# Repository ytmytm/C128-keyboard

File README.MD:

# C128 USB Keyboard

This project is designed to allow a modern USB keyboard to be used with a Commodore 128D/DCR in place of the original Commodore keyboard.

This project was originally forked from [Hartland/C64-Keyboard](https://github.com/Hartland/C64-Keyboard).
I made extensive hardware and software changes to support the full C128 keyboard.

I kept only the USB interface, as PS/2 keyboards are becoming retro themselves.

This project requires a Seeed Studio XIAO SAMD21, which has a USB-C socket. I use a USB-C male to USB-A female OTG adapter to connect a standard PC keyboard.

-- Maciej 'YTM/Elysium' Witkowiak

# Features

- Works with compatible USB HID boot-protocol keyboards, including wireless models with USB receivers.
- Maps all C128 keys, including `40/80`, `CAPS` and the second set of cursor keys.
- Provides four keyboard layouts that can be switched on the fly.
- Supports a VICE-style joystick mode on the keypad, selected with NumLock or Shift+NumLock (may not work with some games).
- Supports an external power supply for an unmodified C128DCR.
- Supports an OLED display.
- Can be plugged directly into the keyboard port or mounted internally.

# PCB and schematic

Use KiCad to open the current [schematic](kicad-c128keyb/kicad-c128keyb.kicad_sch)
and [PCB](kicad-c128keyb/kicad-c128keyb.kicad_pcb) in the
[kicad-c128keyb](kicad-c128keyb/) folder. The legacy `kicad-c128keyb.sch` and
`.net` files describe an older Pro Micro/MT8808 design; use the `.kicad_sch`
and `.kicad_pcb` files for this XIAO/MT8816 adapter.

The [kicad-c128keyb/plots](kicad-c128keyb/plots) folder contains Gerber files ready for manufacturing
and a [PDF schematic](kicad-c128keyb/plots/kicad-c128keyb.pdf).

To order PCBs, open the [shared project on PCBWay](https://www.pcbway.com/project/shareproject/C128_USB_Keyboard_adapter_dcf19251.html) and add the boards to your cart.

## Parts

* Seeed Studio XIAO SAMD21 (SAMD21, not RP2040)
* U1: MT8816 or MT8812
* U2: 74HC/HCT/LS595
* R1, R2, R3: 10 kΩ resistors
* Q1, Q2, Q3: 2N3904 transistors (or another NPN type, such as S9013)
* C1, C2: 100 nF capacitors
* PCB-mount male DB25 connector (option 1)
* 26-pin ribbon cable connector / 2 × 13-pin headers (option 2)
* Pin headers and sockets
* 128 × 32 SSD1306 I²C OLED display (optional)

Check the pinout of any substitute NPN transistor before fitting it to the PCB.

## Connection options

- Plugs directly into the keyboard port when fitted with a male DB25 connector.
- Can use a ribbon cable for either an internal or external connection.
- Can be powered from the keyboard port or an external source, selected by a jumper.
- Can be fitted with a 128 × 32 I²C OLED display for status and debugging.

### Power (C128DCR only)

The C128D supplies +5 V on pin 4 of the keyboard port; the C128DCR does not.
An internal modification can add this connection to the C128DCR.

The photo below shows a wire on the underside of the C128DCR mainboard connecting +5 V from the joystick port to pin 4 of the keyboard port.

If you prefer not to open your C128DCR, you can supply external power from the nearby cassette or joystick port.
In this case, leave jumper JP1 open and connect +5 V to the `Ext. power` connector. Observe the polarity.

Options:

- JP1 open: supply power through `Ext. power` for an unmodified C128DCR.
- JP1 closed: leave `Ext. power` disconnected; use this setting for a C128D or a modified C128DCR.

### Flat cable: 26 pins (socket) to 25 pins (DB25 male)

If you prefer not to have the adapter protruding from the computer, you can make an extension cable.

You need:

* A 26-wire ribbon cable
* 26-pin ribbon cable connectors (a male PCB connector and a female cable connector)
* A male DB25 insulation-displacement connector for ribbon cable

Steps:

1. Solder the 26-pin male ribbon cable connector to J1.
2. Crimp the 26-pin female connector onto the cable, aligning the red wire (wire 1) with the triangular pin-1 mark.
3. Separate wire 26 (at the opposite edge from the red wire) from the ribbon and cut it as close to the female connector as possible.
4. Align the cable with the DB25 connector and crimp it, checking that the red wire connects to pin 1.

# Firmware

The sketch is in [SEEED/C128_keyboard](SEEED/C128_keyboard/). Keep all files in
that folder together when copying it to another computer.

## Install and upload with Arduino IDE

1. Install the **Seeed SAMD Boards** package and select the **Seeeduino XIAO**
   board (SAMD21). Follow the [Seeed setup instructions](https://wiki.seeedstudio.com/Seeeduino-XIAO/#software)
   to add the board package URL if necessary.
2. Use the Library Manager to install **[U8g2](https://github.com/olikraus/U8g2_Arduino)**
   and **[ShiftRegister74HC595](https://github.com/Simsso/ShiftRegister74HC595)**.
   U8g2 is required to compile the sketch even when no OLED is connected.
3. Download **`SEEED/C64_USB_Host_Library_SAMD.zip` from this repository**
   ([download the matching ZIP](SEEED/C64_USB_Host_Library_SAMD.zip)). In the IDE,
   choose **Sketch > Include Library > Add .ZIP Library** and select that local
   file. Alternatively, replace the installed library with this checkout's
   [source directory](SEEED/C64_USB_Host_Library_SAMD).
   A generic USB host library is not a substitute for this modified version.
4. Open [C128_keyboard.ino](SEEED/C128_keyboard/C128_keyboard.ino) in the Arduino IDE.
5. Disconnect the USB keyboard/OTG adapter and connect the XIAO's USB-C port
   to the computer with a USB data cable. Select the board's port and upload.
   If the port is missing or upload fails, enter the bootloader as described
   below, select its port, and try again.
6. Disconnect the programming cable, reconnect the keyboard through the OTG
   adapter, and power the adapter using the configuration described above.

Install the matching USB library on **the computer that compiles the sketch**.
Updating only the sketch or the Git checkout does not update an independently
installed library. The sketch rejects older library headers at compile time.

### Replacing the library on Windows

1. Close Arduino IDE and locate the sketchbook folder shown in its Preferences.
   Its library directory is usually `Documents\Arduino\libraries`, but the
   sketchbook may be elsewhere, including under OneDrive.
2. Move the old `C64_USB_Host_Library_SAMD` folder outside the `libraries`
   directory, then extract the current ZIP there. Replace the whole folder.
3. Check that the resulting layout is
   `libraries\C64_USB_Host_Library_SAMD\library.properties`, with no extra
   nested `C64_USB_Host_Library_SAMD` directory.
4. Restart the IDE and compile again. If multiple libraries are reported for
   `KeyboardController.h`, enable verbose compilation output and check the
   selected path. Remove or replace any outdated copy being selected.

On systems that support symbolic links, the installed library directory can
instead link to this checkout's `SEEED/C64_USB_Host_Library_SAMD` directory.
Move the old copy outside `libraries` and restart the IDE after changing it.

## Compile with the checkout's library using Arduino CLI

Run from the repository root. The Seeed SAMD board package, U8g2 and
ShiftRegister74HC595 must already be installed for Arduino CLI.

Bash (Linux/macOS):

```sh
arduino-cli compile \
  --fqbn Seeeduino:samd:seeed_XIAO_m0 \
  --library "$PWD/SEEED/C64_USB_Host_Library_SAMD" \
  SEEED/C128_keyboard
```

PowerShell (Windows):

```powershell
arduino-cli compile --fqbn Seeeduino:samd:seeed_XIAO_m0 --library ".\SEEED\C64_USB_Host_Library_SAMD" ".\SEEED\C128_keyboard"
```

The explicit [`--library` option](https://arduino.github.io/arduino-cli/1.5/sketch-build-process/#dependency-resolution)
has priority over libraries installed in the sketchbook. These commands use
the source directory directly, so no USB library ZIP installation is needed.
They compile the firmware; use the Arduino IDE or an appropriate CLI upload
command to upload it to the board.

## Entering the bootloader (double reset)

The original XIAO SAMD21 has reset pads rather than an onboard reset button.
To enter its bootloader:

1. Disconnect the keyboard/OTG adapter and connect the XIAO to the computer
   with a USB data cable.
2. Briefly bridge the two **RST reset pads twice in quick succession**, removing
   the bridge between the two touches. See [Seeed's reset-pad illustration](https://wiki.seeedstudio.com/Seeeduino-XIAO/#enter-bootloader-mode)
   for the pad locations. If your board has a reset button, press it twice.
3. The bootloader LED should pulse. With a UF2-enabled bootloader, a removable
   drive normally named **Arduino** appears, containing `INFO_UF2.TXT`.
   A bootloader serial port may also appear; on Windows its COM number may
   differ from the application port. Select that port for an IDE upload.

A single reset restarts the application. **Print Screen on the USB keyboard
only resets the adapter's keys and settings; it does not enter the bootloader.**

## Uploading a UF2 file by copying it to the boot drive

The [XIAO SAMD21 UF2 bootloader supports drag-and-drop flashing](https://wiki.seeedstudio.com/Seeeduino-XIAO-CircuitPython/#installing-circuitpython).
With a UF2-enabled bootloader and a UF2 build of **this project's firmware for
XIAO SAMD21**, no Arduino IDE is needed on the computer doing the upload:

1. Enter the bootloader using the double-reset procedure above.
2. Copy the firmware `.uf2` file to the **Arduino** removable drive using
   Windows File Explorer or your system's file manager.
3. Wait for copying to finish. The board normally restarts automatically and
   the boot drive disappears. Reconnect the keyboard/OTG adapter for use.

Prebuilt firmware is produced by the [Firmware build workflow](.github/workflows/firmware.yml)
and can be downloaded from a successful Actions run or a GitHub Release after
its build completes. The UF2 already contains the compiled libraries; its
recipient does not need Arduino IDE or the USB library ZIP.

Compiled binaries are not tracked in Git. The library ZIP is installed on the
build computer; it is not copied to the board's boot drive.
A `.bin` file cannot be used by simply renaming it to `.uf2`.

### Creating a UF2 from an Arduino build

1. Build for **Seeeduino XIAO (SAMD21)** with the matching USB library, then
   use **Sketch > Export Compiled Binary** in the Arduino IDE. Locate the
   application binary, normally named `C128_keyboard.ino.bin`.
2. Download [uf2conv.py](https://github.com/microsoft/uf2/blob/master/utils/uf2conv.py)
   and [uf2families.json](https://github.com/microsoft/uf2/blob/master/utils/uf2families.json)
   from Microsoft's UF2 project and place them alongside the binary.
3. In that directory, run the conversion with Python 3 (adjust the binary
   filename if your build uses a different one):

   ```sh
   python uf2conv.py --convert --family SAMD21 --base 0x2000 --output C128_keyboard.uf2 C128_keyboard.ino.bin
   ```

Use the application binary from this sketch's XIAO SAMD21 build, without a
bootloader image prepended. The `0x2000` application address matches the
[Seeed XIAO linker configuration](https://github.com/Seeed-Studio/ArduinoCore-samd/blob/master/variants/XIAO_m0/linker_scripts/gcc/flash_with_bootloader.ld).
The conversion only creates the UF2 file; copy it to the boot drive separately.

## OLED and firmware version

The optional display is a **128 × 32 SSD1306 I²C OLED at address `0x3C`**.
The firmware probes for it at startup and skips display operations if it does
not respond. The keyboard and joystick functions work without it.

The OLED shows the firmware release date below startup USB status messages,
for example `USB Configuring` / `FW 2026-10-30`. The version also appears below
`USB Running`. Status messages are cleared after about five seconds of
inactivity; key events replace them with the key display.

Set the release date in [firmware_version.h](SEEED/C128_keyboard/firmware_version.h)
when preparing a new firmware release. Recompiling the same source does not
change its version.

## Keyboard compatibility

The USB driver uses HID boot-protocol reports with six ordinary key slots and
separate modifier bits. A keyboard that only supports a proprietary or
NKRO-only report format may not work. Wireless keyboards need a compatible
USB receiver; Bluetooth-only keyboards cannot connect directly.

The adapter reads raw USB HID usages, so the PC's operating-system keyboard
layout does not configure it. The symbolic maps assume US-style key labels.
For troubleshooting, Right Shift should appear as HID usage `0xE5` with
modifier mask `0x20`. `getOemKey()` returns the HID usage; `getKey()` returns
ASCII and is not used to map the Commodore keyboard matrix.

# Keyboard mapping

Key maps are defined in [SEEED/C128_keyboard/keymaps.h](SEEED/C128_keyboard/keymaps.h). You can modify existing ones or add your own.

After defining a new keymap, add it to the `keymaps[]` array at the bottom of the file. The first entry is the default layout.

Press **Pause** to cycle through C128 positional → C128 symbolic → C64
positional → C64 symbolic → C128 positional. Startup and **Print Screen**
reset select C128 positional. Selection is not saved across power cycles.
The C64 names describe keyboard layouts; the hardware still uses the C128D/DCR
keyboard connector.

The following controls apply in all four layouts:

| USB key | Action |
| --- | --- |
| Print Screen | Reset adapter keys and settings to startup defaults; does not reset the C128 |
| Scroll Lock | Toggle Shift Lock |
| Pause | Select the next keymap |
| Caps Lock | RUN/STOP; use Scroll Lock for Shift Lock |
| Page Up or AltGr | Hold RESTORE while the key is held |
| NumLock | Toggle joystick mode and select port 2 |
| Shift+NumLock | Toggle joystick mode and select port 1 |

After resetting the adapter, release any keys that were held during the reset.
Disconnecting the USB keyboard releases held keys, joystick outputs, RESTORE
and Shift Lock, but preserves the selected keymap and joystick mode.

## C128 positional (default)

The top row follows the C128 keyboard layout. This layout is useful if you are familiar with the original keyboard.

| USB key | C128 key |
|---------|----------|
| ESC | RUN/STOP |
| Tab | CTRL |
| Caps Lock | RUN/STOP |
| F1 | ESC |
| F2 | TAB |
| F3 | ALT |
| F4 | CAPS/DIN (toggle) |
| F5 | HELP |
| F6 | LINEFEED |
| F7 | 40/80 (toggle) |
| F8 | NO SCROLL |
| F9 | F1/F2 |
| F10 | F3/F4 |
| F11 | F5/F6 |
| F12 | F7/F8 |
| Print Screen | reset adapter keys and settings |
| Scroll Lock | Shift Lock |
| Pause | switch to next keymap |
| Insert | POUND |
| Home | CLR/HOME |
| Page Up | RESTORE |
| End | RUN/STOP |
| NumLock | enable/disable joystick #2 on keypad |
| Shift+NumLock | enable/disable joystick #1 on keypad |
| Keypad digits, `+`, `-`, Enter and `.` | C128 keypad equivalents (outside joystick mode) |
| left CTRL | C= key |
| left SHIFT | left SHIFT |
| left ALT | C128 top cursor down |
| left Win | C128 top cursor up |
| Menu/Application | C128 top cursor left |
| right CTRL | C128 top cursor right |
| right SHIFT | right SHIFT |
| AltGr | RESTORE |
| right Win | ignored |

## C128 symbolic

Symbols follow US-style PC keycaps; for example, Shift+2 produces `@` rather than `"`.

Other changes:

- C128 top cursor keys are available via Shift+arrow keys.
- Both Ctrl keys map to CTRL.
- Both Windows keys map to the C= key.
- Left Alt maps to C128 ALT.
- AltGr maps to RESTORE.

The function row and several editing keys also differ from C128 positional:

| USB key | C128 key/action |
| --- | --- |
| Esc | ESC |
| Tab | TAB |
| F1–F8 | F1–F8 (even function keys use synthetic Shift) |
| F9 | HELP |
| F10 | NO SCROLL |
| F11 | 40/80 (toggle) |
| F12 | CAPS/DIN (toggle) |
| Insert | INST/DEL with Shift (insert) |
| Delete | INST/DEL |
| Shift+Return | LINEFEED |

Menu/Application still maps to the C128 top left cursor key.

## C64 positional

This uses the positional character and modifier mappings, with these changes:

- Keypad digits, `+`, `-`, Enter and `.` map to the Commodore's main digit
  keys, PLUS, MINUS, RETURN and full stop.
- F1–F8 map to the corresponding Commodore function keys, using synthetic
  Shift for even-numbered function keys.
- F9 and F10 are ignored.
- F11 toggles 40/80; F12 toggles CAPS/DIN.

For this reason, the C128 positional function-row table does not apply to this
layout. The common adapter controls and joystick mode are still available.

## C64 symbolic

This uses the C128 symbolic mapping, except that keypad digits, `+`, `-`,
Enter and `.` map to the Commodore's main digit keys, PLUS, MINUS,
RETURN and full stop. Joystick mode overrides keypad direction and FIRE
keys in the same way as in the other layouts.

# Joystick mode

Press **NumLock** to toggle joystick mode and select port 2, or
**Shift+NumLock** to toggle it and select port 1. Both combinations toggle
the same on/off state. To change ports while the mode is enabled, first
turn it off, then enable the desired port with the appropriate combination.

The OLED reports the selected mode and port. The USB library toggles the
NumLock LED separately; it is not resynchronised when Print Screen resets
the adapter, so the LED alone is not a reliable mode indicator after a reset.

The keypad directions are the same for both joystick ports:

| Keypad key | Direction |
| --- | --- |
| 7 | up + left |
| 8 | up |
| 9 | up + right |
| 4 | left |
| 6 | right |
| 1 | down + left |
| 2 | down |
| 3 | down + right |
| 5, 0, right Ctrl | FIRE |

A diagonal key is equivalent to holding its two direction keys together.
A direction remains active while any held key still requires it. For example,
releasing keypad 1 while holding keypad 4 leaves LEFT active.

This mode is not intended to replace a physical joystick: some games may interpret joystick #2 inputs as keypresses.

# Automated builds and releases

[.github/workflows/firmware.yml](.github/workflows/firmware.yml) runs host tests
and builds for **XIAO SAMD21** on firmware-related pushes, pull requests,
manual Actions runs, and published GitHub Releases. It explicitly selects the
USB library from this checkout. Arduino CLI, the board package, external
libraries and the official UF2 converter are pinned to specific versions.

Each successful run provides a downloadable artifact containing:

- `.uf2` for copying to the bootloader drive;
- `.bin` application image and `.elf` debug symbols;
- `.json` with the firmware date, source commit and tool versions;
- `SHA256SUMS.txt` for integrity checks.

Filenames contain the board name, firmware date and abbreviated source commit.
Actions artifacts are retained for 30 days. For a lasting download, publish a
GitHub Release from a tag named **`YYYY-MM-DD` or `vYYYY-MM-DD`**, matching
[firmware_version.h](SEEED/C128_keyboard/firmware_version.h), for example
`v2026-10-30`. The workflow rebuilds the tagged source and attaches the files
to that release after tests and verification pass. A tag/date mismatch fails
the build instead of attaching incorrectly labelled files.

Publishing a release is a manual maintainer action; branch pushes and pull
requests only produce build artifacts. The workflow does not create releases
or push tags. To change the tested dependency versions, edit the workflow's
`env` section and rerun the build.

## Release checklist (maintainers)

**Use `v<firmwareVersion>` as the release tag.** For example, if
`firmware_version.h` contains `"2026-10-30"`, use **`v2026-10-30`**.

1. Set the release date in [firmware_version.h](SEEED/C128_keyboard/firmware_version.h).
2. Commit and push the source, including that version and the workflow.
3. On GitHub, open **Releases > Draft a new release**. Select or create the
   tag `vYYYY-MM-DD` using the exact date from the header. Point the tag at
   the tested commit/branch containing the updated firmware and workflow.
4. Click **Publish release**. Saving a draft alone does not start this build.
5. Wait for **Firmware build** to succeed and check that the release has its
   `.uf2` and `SHA256SUMS.txt` assets before sharing it.

The packager also accepts the date without the `v` prefix, but use the
`vYYYY-MM-DD` convention for project releases. A different date is rejected.

The packager checks the application's vector table, SAMD21 family ID, flash
addresses and every UF2 payload byte against the compiled BIN. These checks
validate the file format and target; hardware testing is still required.

# Development and tests

With Python 3 and GCC's `g++` with AddressSanitizer and UndefinedBehaviorSanitizer
available (for example, on Linux or WSL), run from the repository root:

```sh
python3 tests/test_keyboard_events.py
python3 -m unittest discover -s tests -p 'test_firmware_artifacts.py' -v
```

The host tests compile the actual event-handling functions as C++14, with
`-Wall -Wextra -Werror`. They use mocked USB transport, GPIO and OLED drawing;
they do not replace an Arduino build or a hardware test. See
[tests/README.md](tests/README.md) for coverage and hardware checks.

After changing the bundled USB library, rebuild its tracked ZIP:

```sh
python3 tools/package_usb_library.py
```

The host tests verify that the ZIP matches the source directory. Both must
be committed together when that library changes. Firmware-only changes do
not require a new USB library ZIP. On Windows, use `python` instead of
`python3` if that is the installed command name.

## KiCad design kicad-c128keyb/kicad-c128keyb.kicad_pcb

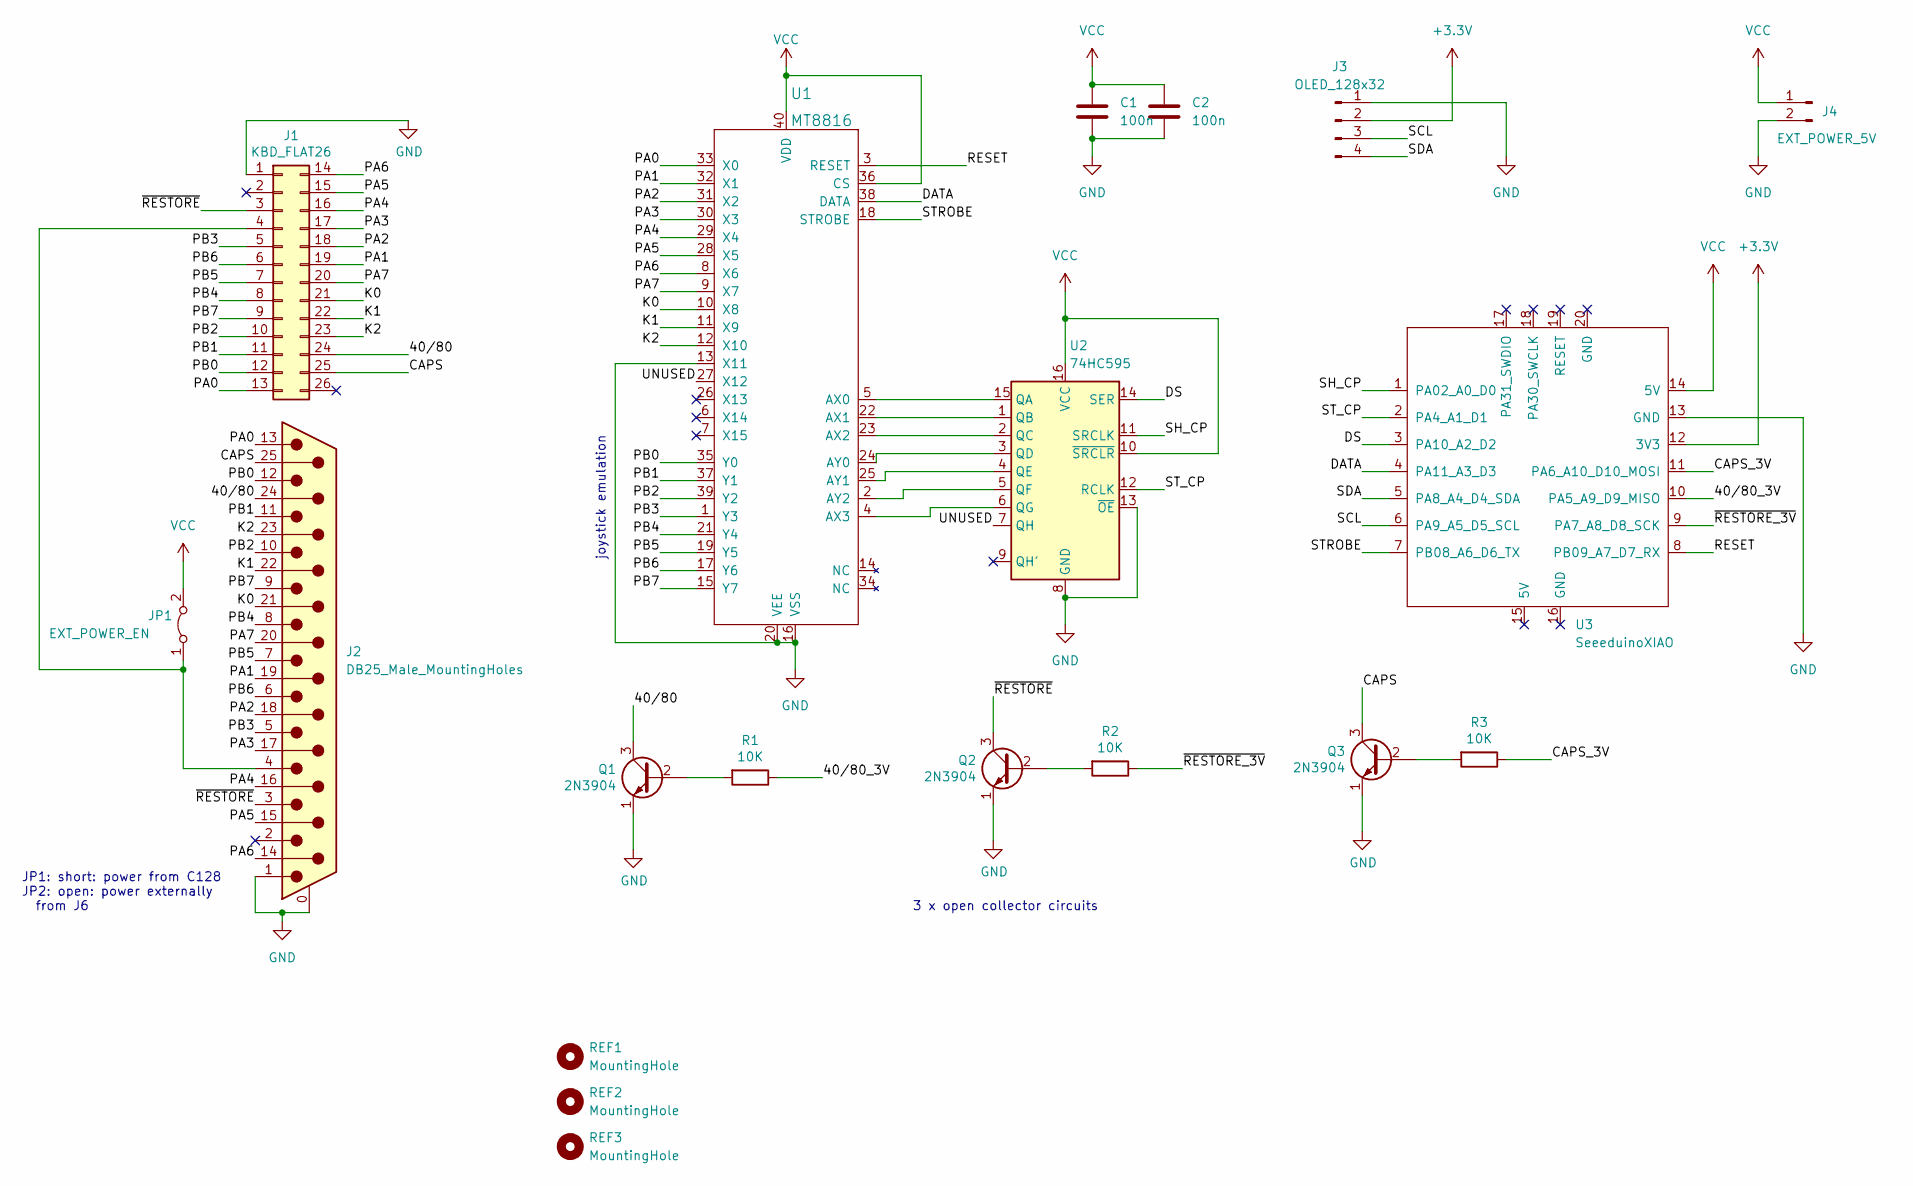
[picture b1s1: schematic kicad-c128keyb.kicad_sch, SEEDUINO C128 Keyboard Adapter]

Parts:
C1, C2: 100n; C_Disc_D4.3mm_W1.9mm_P5.00mm
J1: KBD_FLAT26; PinHeader_2x13_P2.54mm_Vertical
J2: DB25_Male_MountingHoles; DSUB-25_Male_Horizontal_P2.77x2.84mm_EdgePinOffset4.94mm_Ho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
J3: OLED_128x32; PinHeader_1x04_P2.54mm_Vertical
J4: EXT_POWER_5V; PinHeader_1x02_P2.54mm_Vertical
JP1: EXT_POWER_EN; PinHeader_1x02_P2.54mm_Vertical
Q1, Q2, Q3: 2N3904; TO-92_Inline
R1, R2, R3: 10K; R_Axial_DIN0207_L6.3mm_D2.5mm_P7.62mm_Horizontal
REF1, REF2, REF3: MountingHole; MountingHole_2.2mm_M2_Pad_Via
U1: MT8816; DIP-40_W15.24mm_Socket
U2: 74HC595; DIP-16_W7.62mm_Socket
U3: SeeeduinoXIAO; XIAO-Generic-Hybrid-14P-2.54-21X17.8MM

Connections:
+3V3: J3.2, U3.12 (3V3)
/40/80: J1.24, J2.24, Q1.3 (C)
/40/80_3V: R1.1, U3.10 (PA5_A9_D9_MISO)
/CAPS: J1.25, J2.25, Q3.3 (C)
/CAPS_3V: R3.1, U3.11 (PA6_A10_D10_MOSI)
/DATA: U1.38 (DATA), U3.4 (PA11_A3_D3)
/DS: U2.14 (SER), U3.3 (PA10_A2_D2)
/K0: J1.21, J2.21, U1.10 (X8)
/K1: J1.22, J2.22, U1.11 (X9)
/K2: J1.23, J2.23, U1.12 (X10)
/PA0: J1.13, J2.13, U1.33 (X0)
/PA1: J1.19, J2.19, U1.32 (X1)
/PA2: J1.18, J2.18, U1.31 (X2)
/PA3: J1.17, J2.17, U1.30 (X3)
/PA4: J1.16, J2.16, U1.29 (X4)
/PA5: J1.15, J2.15, U1.28 (X5)
/PA6: J1.14, J2.14, U1.8 (X6)
/PA7: J1.20, J2.20, U1.9 (X7)
/PB0: J1.12, J2.12, U1.35 (Y0)
/PB1: J1.11, J2.11, U1.37 (Y1)
/PB2: J1.10, J2.10, U1.39 (Y2)
/PB3: J1.5, J2.5, U1.1 (Y3)
/PB4: J1.8, J2.8, U1.21 (Y4)
/PB5: J1.7, J2.7, U1.19 (Y5)
/PB6: J1.6, J2.6, U1.17 (Y6)
/PB7: J1.9, J2.9, U1.15 (Y7)
/RESET: U1.3 (RESET), U3.8 (PB09_A7_D7_RX)
/SCL: J3.3, U3.6 (PA9_A5_D5_SCL)
/SDA: J3.4, U3.5 (PA8_A4_D4_SDA)
/SH_CP: U2.11 (SRCLK), U3.1 (PA02_A0_D0)
/STROBE: U1.18 (STROBE), U3.7 (PB08_A6_D6_TX)
/ST_CP: U2.12 (RCLK), U3.2 (PA4_A1_D1)
/UNUSED: U1.27 (X12), U2.7 (QH)
/~RESTORE_3V: R2.1, U3.9 (PA7_A8_D8_SCK)
/~RESTORE: J1.3, J2.3, Q2.3 (C)
GND: C1.2, C2.2, J1.1, J2.0 (PAD), J2.1, J3.1, J4.2, Q1.1 (E), Q2.1 (E), Q3.1 (E), U1.13 (X11), U1.16 (VSS), U1.20 (VEE), U2.8 (GND), U2.13 (~OE), U3.13 (GND)
unnamed: J1.4, J2.4, JP1.1 (A)
unnamed: Q1.2 (B), R1.2
unnamed: Q2.2 (B), R2.2
unnamed: Q3.2 (B), R3.2
unnamed: U1.2 (AY2), U2.5 (QF)
unnamed: U1.4 (AX3), U2.6 (QG)
unnamed: U1.5 (AX0), U2.15 (QA)
unnamed: U1.22 (AX1), U2.1 (QB)
unnamed: U1.23 (AX2), U2.2 (QC)
unnamed: U1.24 (AY0), U2.3 (QD)
unnamed: U1.25 (AY1), U2.4 (QE)
VCC: C1.1, C2.1, J4.1, JP1.2 (B), U1.36 (CS), U1.40 (VDD), U2.10 (~SRCLR), U2.16 (VCC), U3.14 (5V)

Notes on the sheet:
joystick emulation
JP1: short: power from C128 JP2: open: power externally from J6
3 x open collector circuits

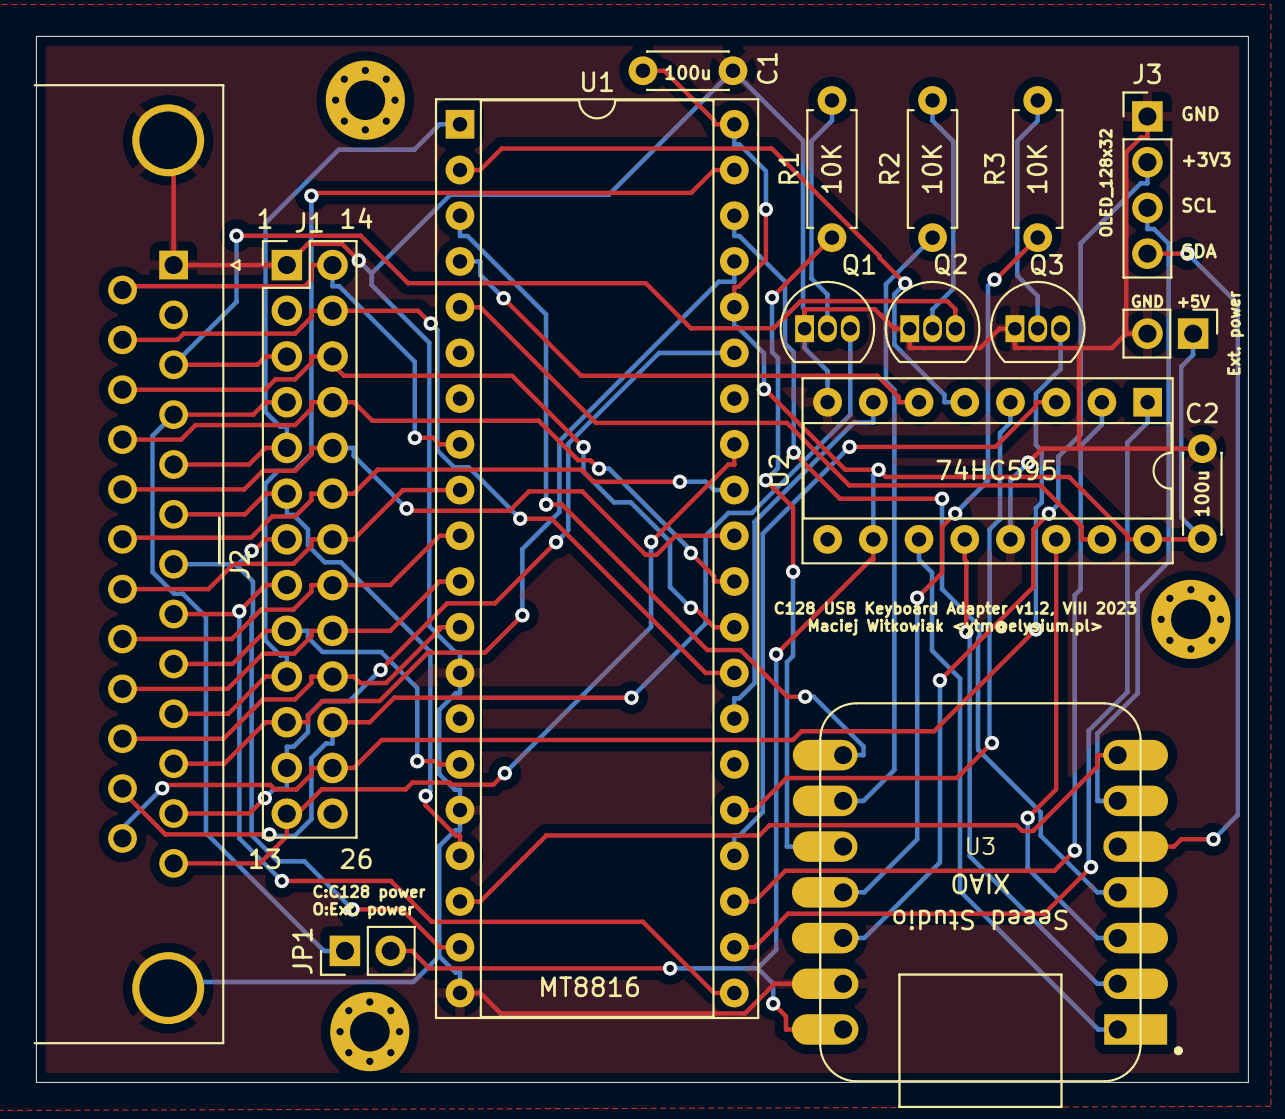
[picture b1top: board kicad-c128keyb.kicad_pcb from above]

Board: 2 copper layers, 67.3 x 58.1 mm, 19 parts (0 on the bottom side), 48 nets.

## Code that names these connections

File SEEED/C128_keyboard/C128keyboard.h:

/*
  C64keyboard - Commodore Keyboard library

  Copyright (c) 2022 Hartland PC LLC
  Written by Robert VanHazinga

  Modified for C128 by Maciej 'YTM/Elysium' Witkowiak


    This program is free software: you can redistribute it and/or modify
    it under the terms of the GNU General Public License as published by
    the Free Software Foundation, either version 3 of the License, or
    (at your option) any later version.

    This program is distributed in the hope that it will be useful,
    but WITHOUT ANY WARRANTY; without even the implied warranty of
    MERCHANTABILITY or FITNESS FOR A PARTICULAR PURPOSE.  See the
    GNU General Public License for more details.

    You should have received a copy of the GNU General Public License
    along with this program.  If not, see <https://www.gnu.org/licenses/>.

*/


#ifndef C128keyboard_h
#define C128keyboard_h

#include <array>

#if defined(ARDUINO) && ARDUINO >= 100
#include "Arduino.h"
#else
#include "WProgram.h"
#endif

//MT88xx control pins
#define ANALOG_SW_DATA      3 // Sets selected cross switch on/off
#define ANALOG_SW_STROBE    6 // Strobe timing pulse
#define ANALOG_SW_RESET     7 // Reset all MT88XX cross switches to off

// I2C DISPLAY
#define SDA_PIN             4 // just for reference, native SEEDUINO XIAO doesn't need these defines
#define SCL_PIN             5

// 74HC595 shift register pins
#define SH_CP_PIN           0 // SRCLK // 11th pin // clock
#define ST_CP_PIN           1 // RCLK  // 12th pin // latch
#define DS_PIN              2 // SER   // 14th pin // data

// bits coming out of shift register connected to MT8812/16
#define ANALOG_SH_AX0     0 // QA (15)
#define ANALOG_SH_AX1     1 // QB (1)
#define ANALOG_SH_AX2     2 // ...
#define ANALOG_SH_AY0     3
#define ANALOG_SH_AY1     4
#define ANALOG_SH_AY2     5
#define ANALOG_SH_AX3     6 // QG (6)
const uint8_t ANALOG_SH_ARRAY[] = { ANALOG_SH_AY2, ANALOG_SH_AY1, ANALOG_SH_AY0, ANALOG_SH_AX2, ANALOG_SH_AX1, ANALOG_SH_AX0 }; // ANALOG_SH_AX3 would be next, but is handled separately
// last, 7th bit unused

// these can't be driven directly, they need to go through transistors for open collector functionality (or 74'xx equivalent chip)
// C128 NMI setup
#define NMI_PIN           8
// C128 40/80
#define C128_40_80_PIN    9
// C128 CAPS
#define C128_CAPS_PIN     10

// C64/128 key codes / USB key codes defines
#include "keymapping.h"

class C64KeyInfo {
  public:
    constexpr C64KeyInfo(const uint16_t c, const char* name) :
    m_keycode(c), m_name(name)
    {};
    constexpr auto get_keycode() const { return m_keycode; }
    constexpr const char* get_name() const { return m_name; };
  private:
    const uint16_t m_keycode;
    const char *m_name;
};

class C128keyboard {
  public:
    C128keyboard();
    void c64key(uint16_t c, bool kpress, uint8_t kc);
    uint16_t mapkeycode(uint8_t kc);
    void clearAllKeys(void);
    void updateShiftSwitches(void);
    constexpr uint8_t getNumKeyMaps(void);
    const char* getCurrentKeyMapName(void);
  private:
    // A saved mapping can drive one matrix switch or a joystick diagonal.
    // Actions such as RESTORE must never alias a physical matrix address.
    static constexpr std::array<uint8_t, 2> getMatrixSwitches(uint16_t mapped) {
      const uint16_t primary = mapped & ~(MOD_SHIFT | MOD_JOY2 | MOD_JOY_UP | MOD_JOY_DOWN);
      if (primary >= 128) return {{0xff, 0xff}};
      const bool port2 = mapped & MOD_JOY2;
      uint8_t vertical = 0xff;
      if (mapped & MOD_JOY_UP) vertical = port2 ? JOY2_UP : JOY1_UP;
      else if (mapped & MOD_JOY_DOWN) vertical = port2 ? JOY2_DOWN : JOY1_DOWN;
      return {{static_cast<uint8_t>(primary), vertical}};
    }
};

class C64Key {
  public:
    constexpr C64Key(const int16_t keycode, const uint16_t unshifted, const uint16_t shifted) :
    m_keycode(keycode), m_unshifted(unshifted), m_shifted(shifted)
    {};
    constexpr auto get_keycode() const { return m_keycode; }
    constexpr uint16_t get(bool shifted = false) const {
      return shifted ? m_shifted : m_unshifted;
    }
  private:
    const int16_t m_keycode;
    const uint16_t m_unshifted, m_shifted;
};

using ModifierMap = std::array<uint16_t, 8>;

class C64KeyMap {
  public:
    constexpr C64KeyMap(const char* name, const C64Key *map, const uint16_t mapsize, const ModifierMap &mods) :
    m_name(name), m_map(map), m_mapsize(mapsize), m_mods(mods)
    {};
    constexpr const char* getName() const { return m_name; };
    constexpr const ModifierMap &getMods() const { return m_mods; };
    constexpr C64Key getKey(uint8_t keycode) const {
      for (uint16_t i = 0; i < m_mapsize; ++i) {
        if (m_map[i].get_keycode() == keycode) {
          return m_map[i];
        }
      }
      return C64Key(0, IGNORE_KEYCODE, IGNORE_KEYCODE);
    }
  private:
    const char *m_name;
    const C64Key *m_map;
    const uint16_t m_mapsize;
    const ModifierMap &m_mods;
};

#endif

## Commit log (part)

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2023-12-29 clean import of https://github.com/gdsports/USB_Host_Library_SAMD
2023-12-29 apply changes marked as C64_USB_Host_Library_SAMD by https://github.com/Hartland/C64-Keyboard
2023-12-29 archive library to be unpacked in Arduino libraries folder
2023-12-29 documentation and support files
2023-12-29 ignore some files
2023-12-29 KiCad project and plots
2023-12-29 clean source code import
2023-12-29 license inherited from https://github.com/Hartland/C64-Keyboard
2023-12-29 cropped
2023-12-29 initial docs
2023-12-29 note about OTG adapter
2023-12-29 complete renaming C64keyboard class
2023-12-30 move image to media/ folder
2023-12-30 photos
2023-12-30 more pictures
2024-11-02 make it possible to run without OLED display connected
2024-11-02 register/unregister original keycodes to correctly identify released keys
